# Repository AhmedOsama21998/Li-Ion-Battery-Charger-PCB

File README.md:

# Li-Ion Battery Charger PCB

A compact single-cell lithium-ion/lithium-polymer battery charger PCB designed in KiCad 9. The circuit is based on the Microchip MCP73831-2 charge-management controller and includes a Micro-USB power input, battery connector, and status indicators.

> **Project status:** Design only. This repository does not claim that the PCB has been fabricated, assembled, or tested. Verify the design against the exact component datasheets and perform appropriate electrical and thermal testing before practical use.

## Preview

### 3D PCB View

### Schematic

## Main Features

- MCP73831-2 single-cell Li-ion/Li-Po charge controller
- Micro-USB connector used as the 5 V input
- Two-pin battery connector
- Charge-status indicator driven by the controller's `STAT` output
- Additional power indicator LED
- Compact PCB layout designed in KiCad 9

## Key Components

| Reference | Component | Value / part |
|---|---|---|
| U1 | Battery charge controller | MCP73831-2-OT |
| J2 | Input connector | Micro-USB Type-B |
| J1 | Battery connector | 2-pin connector |
| R2 | Charge-current programming resistor | 2 kΩ |
| R1 | Status LED series resistor | Value must be confirmed in the schematic/BOM |
| R3 | Power LED series resistor | 470 Ω |
| C1, C2 | Capacitors | Values must be confirmed in the schematic/BOM |
| D1 | Charge-status LED | LED |
| D2 | Power indicator LED | LED |

The charge current is set by the programming resistor connected to `PROG`; confirm the intended current using the MCP73831-2 datasheet and the exact resistor value before use. Do not assume the board is suitable for every cell or battery pack.

## Connector Notes

### Micro-USB input (J2)
- `VBUS`: 5 V input
- `GND`: ground
- `D+`, `D-`, and `ID`: not used in this design
- Shield is connected to ground in the schematic

### Battery connector (J1)
- Pin 1: `VBat`
- Pin 2: `GND`

Check connector orientation and polarity against the PCB silkscreen before connecting a battery.

## Repository Structure

```text
Li-Ion-Battery-Charger-PCB/
├── KiCad/
│   ├── Li_Battery_Charger.kicad_pro
│   ├── Li_Battery_Charger.kicad_sch
│   └── Li_Battery_Charger.kicad_pcb
├── Images/
│   ├── li-ion-charger-3d-view.png
│   └── li-ion-charger-schematic.png
├── Documentation/
└── README.md
```

## Design and Safety Notes

- Intended for a **single-cell 4.2 V nominal-charge-voltage Li-ion/Li-Po battery**, consistent with the MCP73831-2 variant; verify the exact IC suffix and battery specification.
- Confirm the programmed charge current, USB source capability, resistor power ratings, capacitor values/ratings, PCB copper width, thermal dissipation, and component footprints before fabrication.
- This board is a charger circuit, not a complete battery-protection system. Use a cell with appropriate protection or add a suitable protection circuit as required by the application.
- The schematic currently leaves the capacitor values and R1 value unspecified; complete and verify the BOM before fabrication.
- Run KiCad ERC and DRC, review the generated reports, and test the assembled board with a current-limited supply and suitable battery test procedure before relying on it.
- No charging performance, thermal performance, or safety certification is claimed.

## Tools

- KiCad 9
- MCP73831-2 charge controller

## License

This project is released under the MIT License. See [LICENSE](LICENSE).

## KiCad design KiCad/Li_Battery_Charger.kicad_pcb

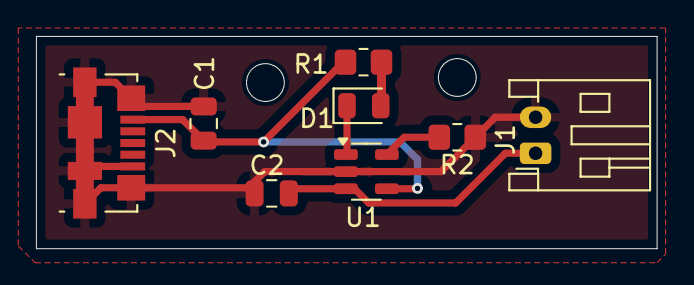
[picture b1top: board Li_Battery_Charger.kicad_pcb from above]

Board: 2 copper layers, 34.5 x 11.8 mm, 8 parts (0 on the bottom side), 6 nets.

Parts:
C1, C2: 4.7uF; C_0805_2012Metric
D1: LED; LED_0805_2012Metric
J1: Conn_01x02_Socket; JST_PH_S2B-PH-K_1x02_P2.00mm_Horizontal
J2: USB_B_Micro; USB_Micro-B_Molex_47346-0001
R1: 470; R_0805_2012Metric_Pad1.20x1.40mm_HandSolder
R2: 2k; R_0805_2012Metric_Pad1.20x1.40mm_HandSolder
U1: MCP73831-2-OT; SOT-23-5

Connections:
/STAT: D1.1 (K), U1.1 (STAT)
/V+: C1.1, J2.1 (VBUS), R1.2, U1.4 (V_{DD})
/VBat: C2.1, J1.1, U1.3 (V_{BAT})
GND: C1.2, C2.2, J1.2, J2.5 (GND), J2.6 (Shield), R2.2, U1.2 (V_{SS})
unnamed: D1.2 (A), R1.1
unnamed: R2.1, U1.5 (PROG)
